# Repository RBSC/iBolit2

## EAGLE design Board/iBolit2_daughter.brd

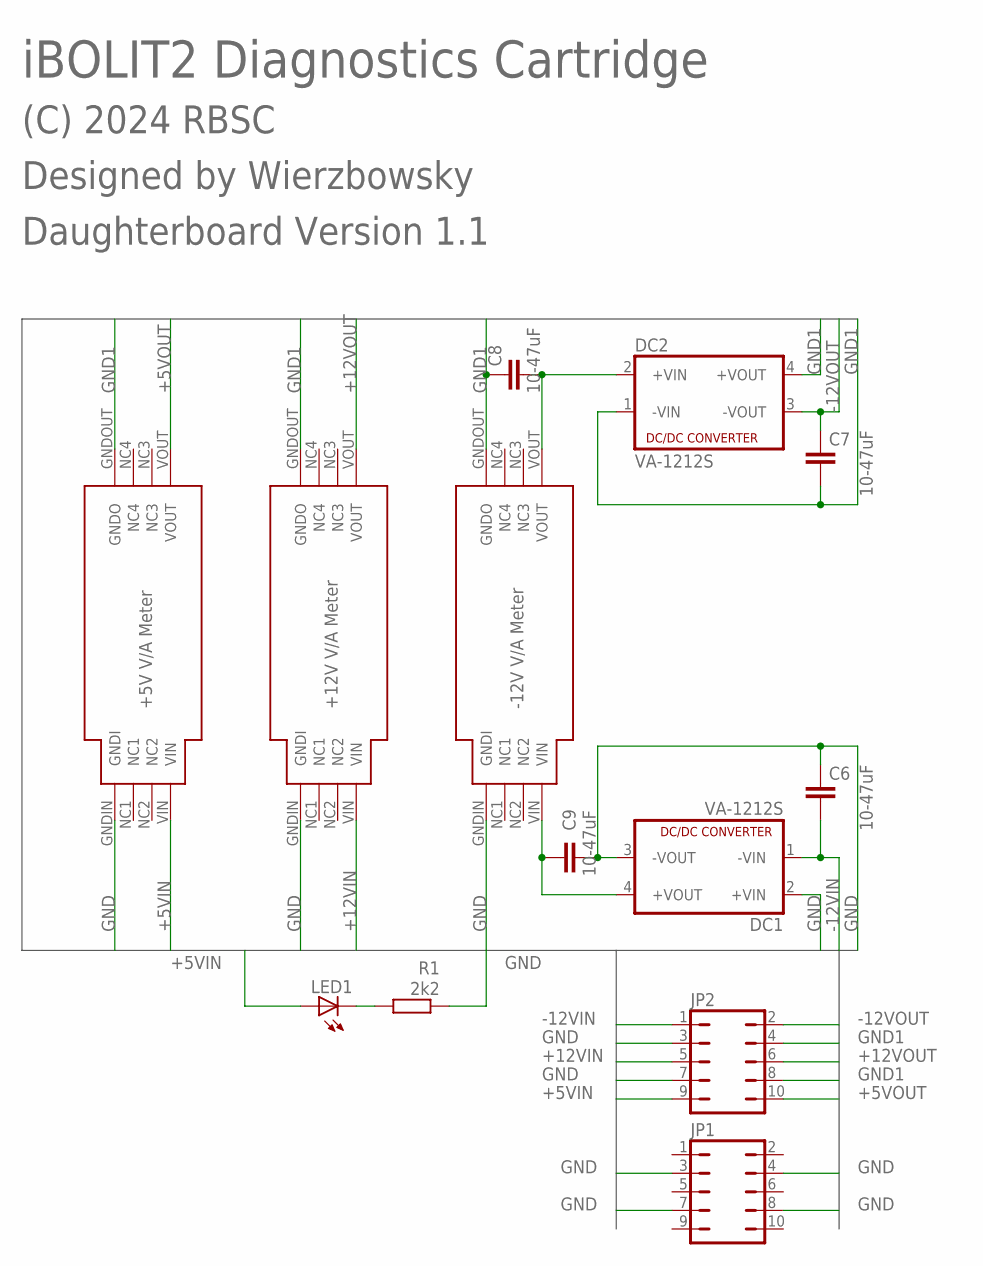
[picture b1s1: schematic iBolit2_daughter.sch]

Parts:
C6, C7, C8, C9: 10-47uF; C1210
DC1, DC2: VA-1212S; 4SIL
JP1, JP2: JP5Q_CUSTOM
LED1: LEDSQR2X5; LED2X5
R1: 2k2; R0805
X1, X2, X3: VA-METER2; VA_METER2

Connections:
+5VIN: JP2.9, LED1.A, X1.VIN
+5VOUT: JP2.10, X1.VOUT
+12VCONVI: C9.1, DC1.4 (+VOUT), X3.VIN
+12VCONVO: C8.2, DC2.2 (+VIN), X3.VOUT
+12VIN: JP2.5, X2.VIN
+12VOUT: JP2.6, X2.VOUT
-12VIN: C6.2, DC1.1 (-VIN), JP2.1
-12VOUT: C7.1, DC2.3 (-VOUT), JP2.2
GND: C6.1, C9.2, DC1.2 (+VIN), DC1.3 (-VOUT), JP1.3, JP1.4, JP1.7, JP1.8, JP2.3, JP2.7, R1.1, X1.GNDIN (GNDI), X2.GNDIN (GNDI), X3.GNDIN (GNDI)
GND1: C7.2, C8.1, DC2.1 (-VIN), DC2.4 (+VOUT), JP2.4, JP2.8, X1.GNDOUT (GNDO), X2.GNDOUT (GNDO), X3.GNDOUT (GNDO)
unnamed: LED1.K (C), R1.2

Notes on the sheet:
+5V V/A Meter
+12V V/A Meter
-12V V/A Meter
iBOLIT2 Diagnostics Cartridge
(C) 2024 RBSC
Designed by Wierzbowsky
Daughterboard Version 1.1

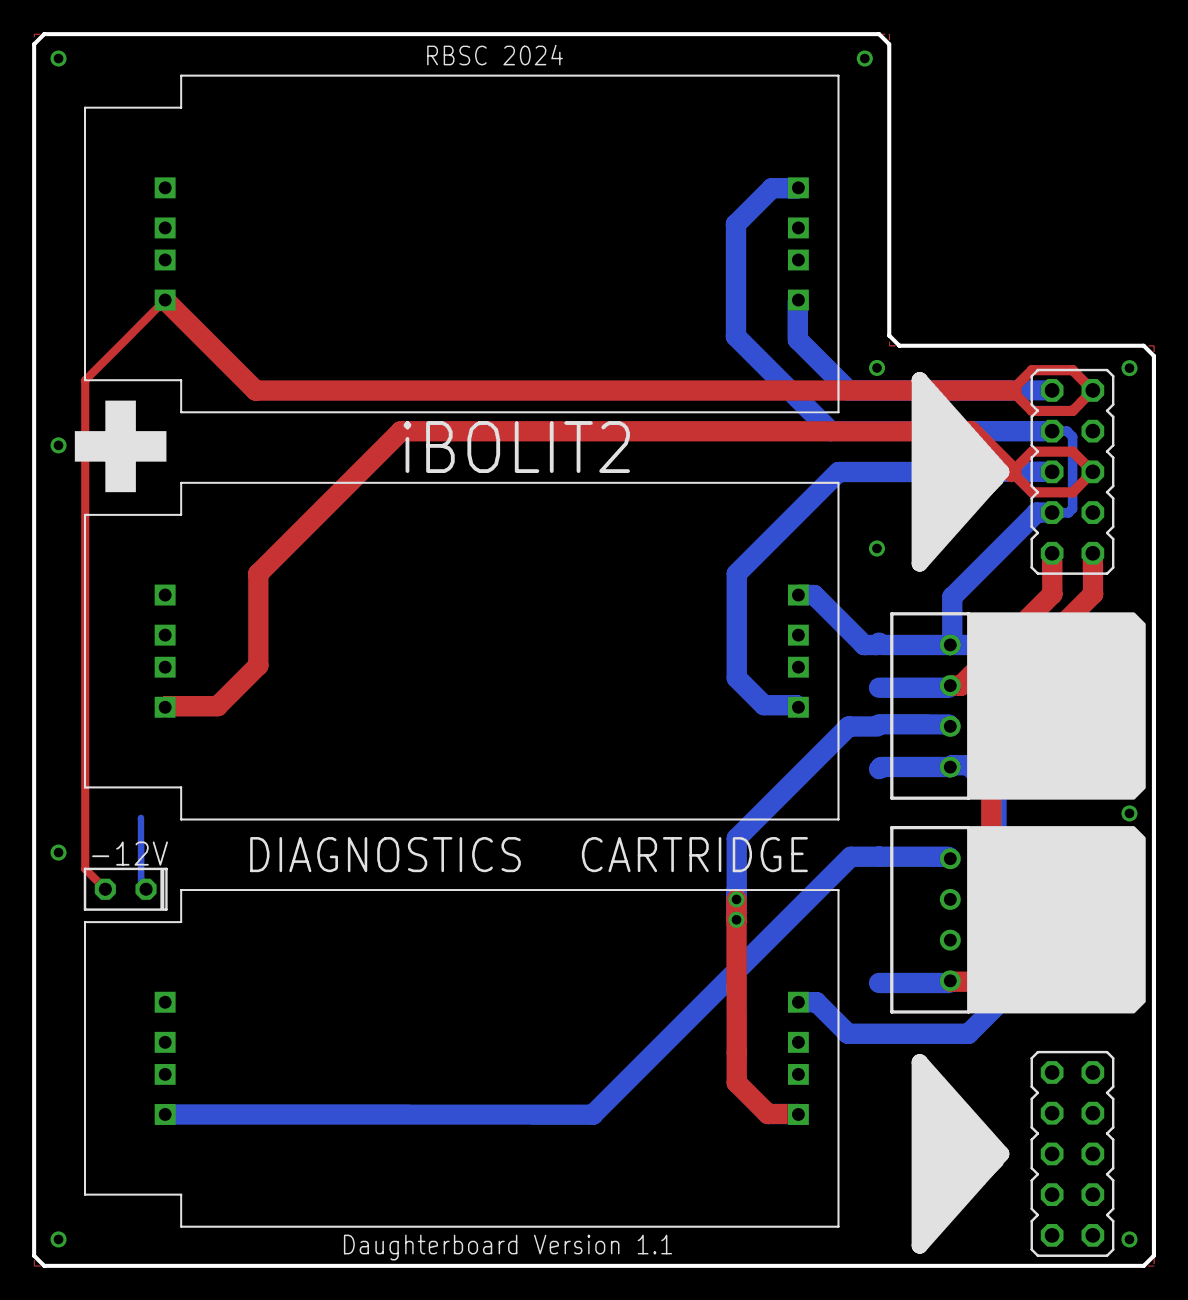
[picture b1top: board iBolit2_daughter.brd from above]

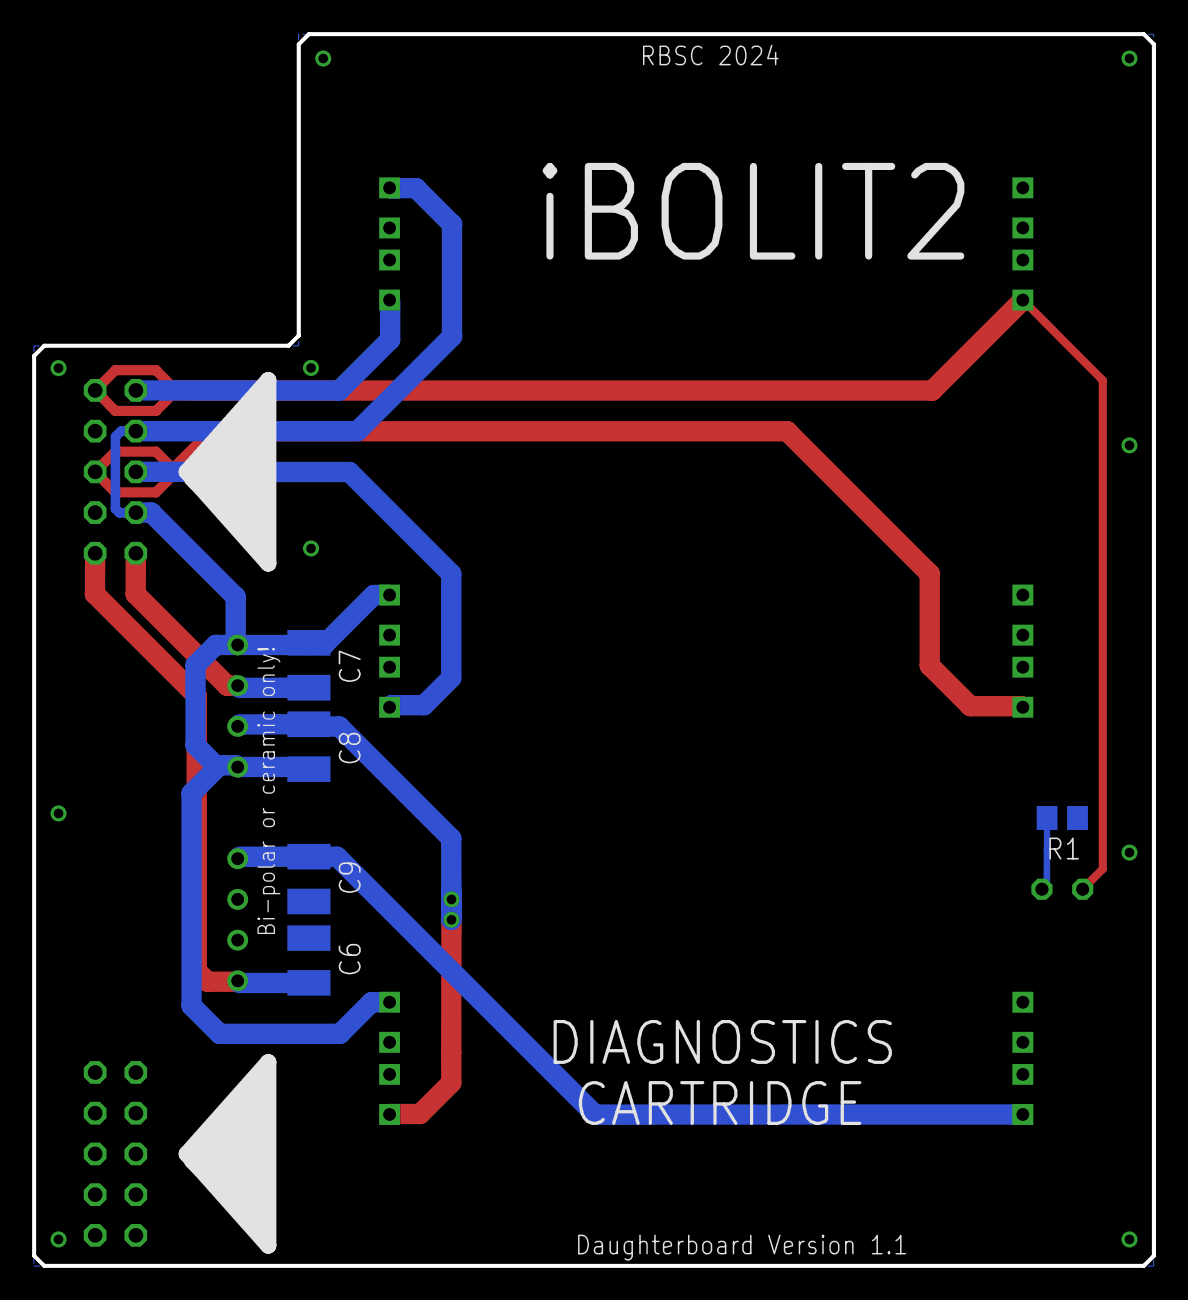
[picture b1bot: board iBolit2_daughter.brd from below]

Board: 2 copper layers, 69.8 x 76.8 mm, 13 parts (5 on the bottom side), 11 nets.

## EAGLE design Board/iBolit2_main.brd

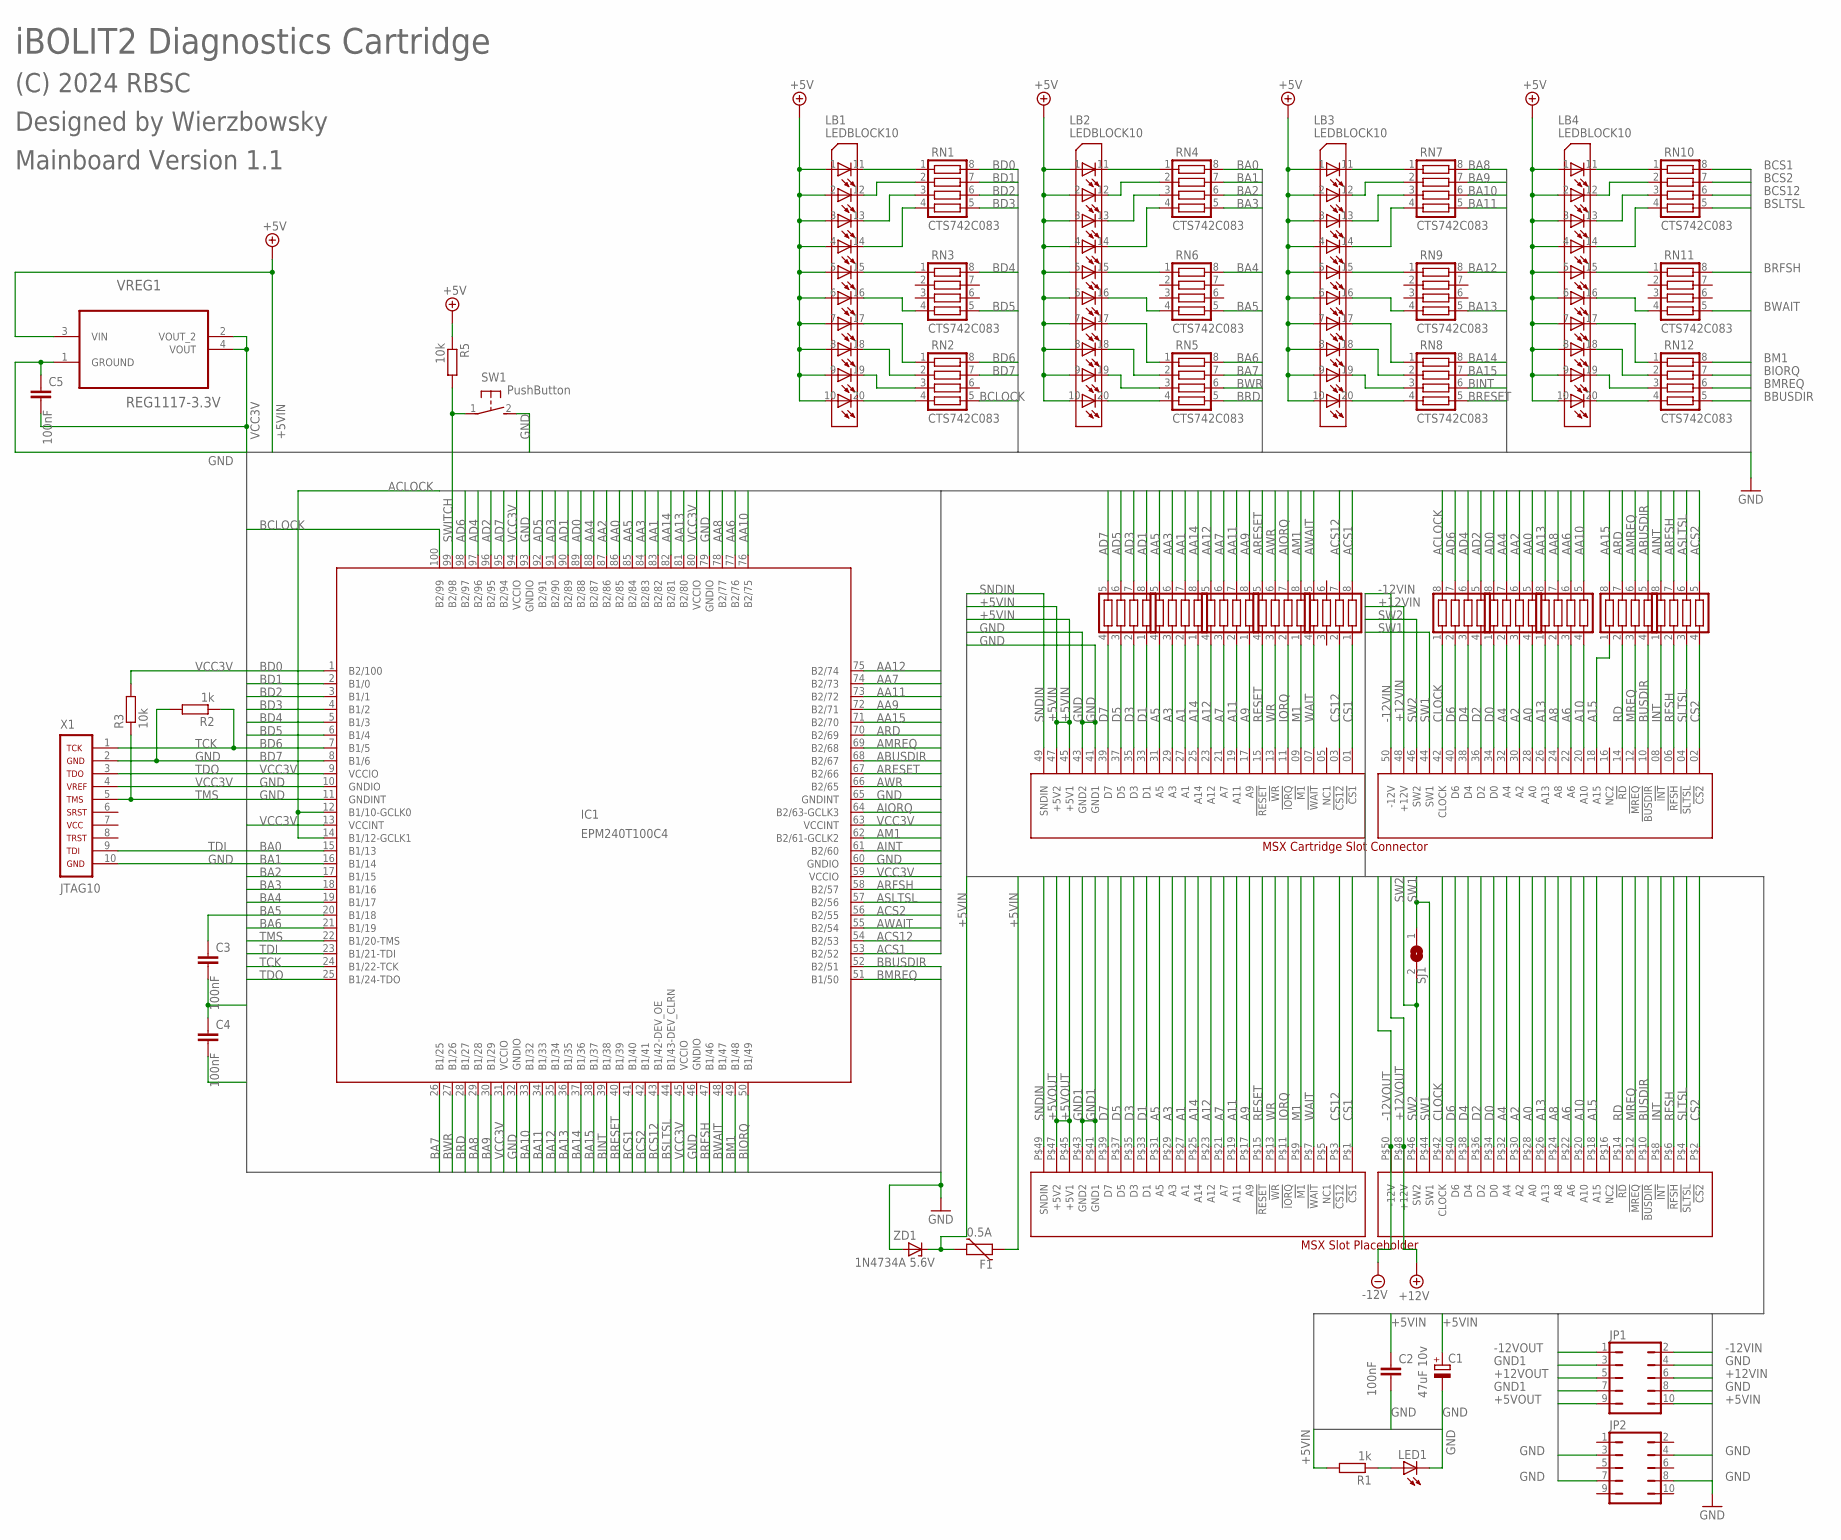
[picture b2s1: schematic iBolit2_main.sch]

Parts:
C1: 47uF 10v; SMC_B
C2, C3, C4, C5: 100nF; C0805
CN1: SLOTCONN; MSX_SLOT_CON
CN2: SLOTPLACEHOLDER; MSX_SLOT_PLP
F1: VARISTORCN1206; CT/CN1206
IC1: EPM240T100C4; TQFP100
JP1, JP2: JP5Q_CUSTOM
LB1, LB2, LB3, LB4: LEDBLOCK10; LB10
LED1: LED5MM
R1, R2: 1k; R0805
R3, R5: 10k; R0805
RN1, RN2, RN3, RN4, RN5, RN6, RN7, RN8, RN9, RN10, RN11, RN12, RN13, RN14, RN15, RN16, RN17, RN28, RN29, RN30, RN31, RN32: CTS742C083
SJ1: SJ
SW1: PushButton; B3F-31XX
VREG1: REG1117-3.3V; SOT230P700X180-4N
X1: JTAG10
ZD1: 1N4734A 5.6V; ZDIO-7.5

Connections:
+5VIN: C1.+, C2.1, CN1.45 (+5V1), CN1.47 (+5V2), F1.1, F1.2, JP1.10, LB1.1 (L1I), LB1.2 (L1I1), LB1.3 (L1I2), LB1.4 (L1I3), LB1.5 (L1I4), LB1.6 (L1I5), LB1.7 (L1I6), LB1.8 (L1I7), LB1.9 (L1I8), LB1.10 (L1I9), LB2.1 (L1I), LB2.2 (L1I1), LB2.3 (L1I2), LB2.4 (L1I3), LB2.5 (L1I4), LB2.6 (L1I5), LB2.7 (L1I6), LB2.8 (L1I7), LB2.9 (L1I8), LB2.10 (L1I9), LB3.1 (L1I), LB3.2 (L1I1), LB3.3 (L1I2), LB3.4 (L1I3), LB3.5 (L1I4), LB3.6 (L1I5), LB3.7 (L1I6), LB3.8 (L1I7), LB3.9 (L1I8), LB3.10 (L1I9), LB4.1 (L1I), LB4.2 (L1I1), LB4.3 (L1I2), LB4.4 (L1I3), LB4.5 (L1I4), LB4.6 (L1I5), LB4.7 (L1I6), LB4.8 (L1I7), LB4.9 (L1I8), LB4.10 (L1I9), R1.2, R5.1, VREG1.3 (VIN), ZD1.C
+5VOUT: CN2.P$45 (+5V1), CN2.P$47 (+5V2), JP1.9
+12VIN: CN1.48 (+12V), JP1.6
+12VOUT: CN2.P$48 (+12V), JP1.5
-12VIN: CN1.50 (-12V), JP1.2
-12VOUT: CN2.P$50 (-12V), JP1.1
A0: CN1.28 (A0), CN2.P$28 (A0), RN29.4
A1: CN1.27 (A1), CN2.P$27 (A1), RN16.2
A2: CN1.30 (A2), CN2.P$30 (A2), RN29.3
A3: CN1.29 (A3), CN2.P$29 (A3), RN16.3
A4: CN1.32 (A4), CN2.P$32 (A4), RN29.2
A5: CN1.31 (A5), CN2.P$31 (A5), RN16.4
A6: CN1.22 (A6), CN2.P$22 (A6), RN30.3
A7: CN1.21 (A7), CN2.P$21 (A7), RN15.3
A8: CN1.24 (A8), CN2.P$24 (A8), RN30.2
A9: CN1.17 (A9), CN2.P$17 (A9), RN15.1
A10: CN1.20 (A10), CN2.P$20 (A10), RN30.4
A11: CN1.19 (A11), CN2.P$19 (A11), RN15.2
A12: CN1.23 (A12), CN2.P$23 (A12), RN15.4
A13: CN1.26 (A13), CN2.P$26 (A13), RN30.1
A14: CN1.25 (A14), CN2.P$25 (A14), RN16.1
A15: CN1.18 (A15), CN2.P$18 (A15), RN32.1
AA0: IC1.86 (B2/85), RN29.5
AA1: IC1.83 (B2/82), RN16.7
AA2: IC1.87 (B2/86), RN29.6
AA3: IC1.84 (B2/83), RN16.6
AA4: IC1.88 (B2/87), RN29.7
AA5: IC1.85 (B2/84), RN16.5
AA6: IC1.77 (B2/76), RN30.6
AA7: IC1.74 (B2/73), RN15.6
AA8: IC1.78 (B2/77), RN30.7
AA9: IC1.72 (B2/71), RN15.8
AA10: IC1.76 (B2/75), RN30.5
AA11: IC1.73 (B2/72), RN15.7
AA12: IC1.75 (B2/74), RN15.5
AA13: IC1.81 (B2/80), RN30.8
AA14: IC1.82 (B2/81), RN16.8
AA15: IC1.71 (B2/70), RN32.8
ABUSDIR: IC1.68 (B2/67), RN32.5
ACLOCK: IC1.12 (B1/10-GCLK0), IC1.14 (B1/12-GCLK1), RN28.8
ACS1: IC1.53 (B2/52), RN13.8
ACS2: IC1.56 (B2/55), RN31.5
ACS12: IC1.54 (B2/53), RN13.7
AD0: IC1.89 (B2/88), RN29.8
AD1: IC1.90 (B2/89), RN17.8
AD2: IC1.96 (B2/95), RN28.5
AD3: IC1.91 (B2/90), RN17.7
AD4: IC1.97 (B2/96), RN28.6
AD5: IC1.92 (B2/91), RN17.6
AD6: IC1.98 (B2/97), RN28.7
AD7: IC1.95 (B2/94), RN17.5
AINT: IC1.61 (B2/60), RN31.8
AIORQ: IC1.64 (B2/63-GCLK3), RN14.7
AM1: IC1.62 (B2/61-GCLK2), RN14.8
AMREQ: IC1.69 (B2/68), RN32.6
ARD: IC1.70 (B2/69), RN32.7
ARESET: IC1.67 (B2/66), RN14.5
ARFSH: IC1.58 (B2/57), RN31.7
ASLTSL: IC1.57 (B2/56), RN31.6
AWAIT: IC1.55 (B2/54), RN13.5
AWR: IC1.66 (B2/65), RN14.6
BA0: IC1.15 (B1/13), RN4.8
BA1: IC1.16 (B1/14), RN4.7
BA2: IC1.17 (B1/15), RN4.6
BA3: IC1.18 (B1/16), RN4.5
BA4: IC1.19 (B1/17), RN6.8
BA5: IC1.20 (B1/18), RN6.5
BA6: IC1.21 (B1/19), RN5.8
BA7: IC1.26 (B1/25), RN5.7
BA8: IC1.29 (B1/28), RN7.8
BA9: IC1.30 (B1/29), RN7.7
BA10: IC1.33 (B1/32), RN7.6
BA11: IC1.34 (B1/33), RN7.5
BA12: IC1.35 (B1/34), RN9.8
BA13: IC1.36 (B1/35), RN9.5
BA14: IC1.37 (B1/36), RN8.8
BA15: IC1.38 (B1/37), RN8.7
BBUSDIR: IC1.52 (B2/51), RN12.5
BCLOCK: IC1.100 (B2/99), RN2.5
BCS1: IC1.41 (B1/40), RN10.8
BCS2: IC1.42 (B1/41), RN10.7
BCS12: IC1.43 (B1/42-DEV_OE), RN10.6
BD0: IC1.1 (B2/100), RN1.8
BD1: IC1.2 (B1/0), RN1.7
BD2: IC1.3 (B1/1), RN1.6
BD3: IC1.4 (B1/2), RN1.5
BD4: IC1.5 (B1/3), RN3.8
BD5: IC1.6 (B1/4), RN3.5
BD6: IC1.7 (B1/5), RN2.8
BD7: IC1.8 (B1/6), RN2.7
BINT: IC1.39 (B1/38), RN8.6
BIORQ: IC1.50 (B1/49), RN12.7
BM1: IC1.49 (B1/48), RN12.8
BMREQ: IC1.51 (B1/50), RN12.6
BRD: IC1.28 (B1/27), RN5.5
BRESET: IC1.40 (B1/39), RN8.5
BRFSH: IC1.47 (B1/46), RN11.8
BSLTSL: IC1.44 (B1/43-DEV_CLRN), RN10.5
BUSDIR: CN1.10 (!BUSDIR), CN2.P$10 (!BUSDIR), RN32.4
BWAIT: IC1.48 (B1/47), RN11.5
BWR: IC1.27 (B1/26), RN5.6
CLOCK: CN1.42 (CLOCK), CN2.P$42 (CLOCK), RN28.1
CS1: CN1.01 (!CS1), CN2.P$1 (!CS1), RN13.1
CS2: CN1.02 (!CS2), CN2.P$2 (!CS2), RN31.4
CS12: CN1.03 (!CS12), CN2.P$3 (!CS12), RN13.2
D0: CN1.34 (D0), CN2.P$34 (D0), RN29.1
D1: CN1.33 (D1), CN2.P$33 (D1), RN17.1
D2: CN1.36 (D2), CN2.P$36 (D2), RN28.4
D3: CN1.35 (D3), CN2.P$35 (D3), RN17.2
D4: CN1.38 (D4), CN2.P$38 (D4), RN28.3
D5: CN1.37 (D5), CN2.P$37 (D5), RN17.3
D6: CN1.40 (D6), CN2.P$40 (D6), RN28.2
D7: CN1.39 (D7), CN2.P$39 (D7), RN17.4
GND: C1.-, C2.2, C3.2, C4.1, C5.1, CN1.41 (GND1), CN1.43 (GND2), IC1.10 (GNDIO), IC1.11 (GNDINT), IC1.32 (GNDIO), IC1.46 (GNDIO), IC1.60 (GNDIO), IC1.65 (GNDINT), IC1.79 (GNDIO), IC1.93 (GNDIO), JP1.4, JP1.8, JP2.3, JP2.4, JP2.7, JP2.8, LED1.K (C), R2.2, SW1.2 (S), VREG1.1 (GROUND), X1.2, X1.10, ZD1.A
GND1: CN2.P$41 (GND1), CN2.P$43 (GND2), JP1.3, JP1.7
INT: CN1.08 (!INT), CN2.P$8 (!INT), RN31.1
IORQ: CN1.11 (!IORQ), CN2.P$11 (!IORQ), RN14.2
M1: CN1.09 (!M1), CN2.P$9 (!M1), RN14.1
MREQ: CN1.12 (!MREQ), CN2.P$12 (!MREQ), RN32.3
unnamed: LED1.A, R1.1
unnamed: LB4.11 (L1O), RN10.1
unnamed: LB4.12 (L1O1), RN10.2
unnamed: LB4.13 (L1O2), RN10.3
unnamed: LB4.14 (L1O3), RN10.4
unnamed: LB4.15 (L1O4), RN11.1
unnamed: LB4.16 (L1O5), RN11.4
unnamed: LB4.17 (L1O6), RN12.1
unnamed: LB4.18 (L1O7), RN12.2
unnamed: LB4.19 (L1O8), RN12.3
unnamed: LB4.20 (L1O9), RN12.4
unnamed: LB1.11 (L1O), RN1.1
unnamed: LB1.12 (L1O1), RN1.2
unnamed: LB1.13 (L1O2), RN1.3
unnamed: LB1.14 (L1O3), RN1.4
unnamed: LB1.15 (L1O4), RN3.1
unnamed: LB1.16 (L1O5), RN3.4
unnamed: LB1.17 (L1O6), RN2.1
unnamed: LB1.18 (L1O7), RN2.2
unnamed: LB1.19 (L1O8), RN2.3
unnamed: LB1.20 (L1O9), RN2.4
unnamed: LB2.11 (L1O), RN4.1
unnamed: LB2.12 (L1O1), RN4.2
unnamed: LB2.13 (L1O2), RN4.3
unnamed: LB2.14 (L1O3), RN4.4
unnamed: LB2.15 (L1O4), RN6.1
unnamed: LB2.16 (L1O5), RN6.4
unnamed: LB2.17 (L1O6), RN5.1
unnamed: LB2.18 (L1O7), RN5.2
unnamed: LB2.19 (L1O8), RN5.3
unnamed: LB2.20 (L1O9), RN5.4
unnamed: LB3.11 (L1O), RN7.1
unnamed: LB3.12 (L1O1), RN7.2
unnamed: LB3.13 (L1O2), RN7.3
unnamed: LB3.14 (L1O3), RN7.4
unnamed: LB3.15 (L1O4), RN9.1
unnamed: LB3.16 (L1O5), RN9.4
unnamed: LB3.17 (L1O6), RN8.1
unnamed: LB3.18 (L1O7), RN8.2
unnamed: LB3.19 (L1O8), RN8.3
unnamed: LB3.20 (L1O9), RN8.4
RD: CN1.14 (!RD), CN2.P$14 (!RD), RN32.2
RESET: CN1.15 (!RESET), CN2.P$15 (!RESET), RN14.4
RFSH: CN1.06 (!RFSH), CN2.P$6 (!RFSH), RN31.2
SLTSL: CN1.04 (!SLTSL), CN2.P$4 (!SLTSL), RN31.3
SNDIN: CN1.49 (SNDIN), CN2.P$49 (SNDIN)
SW1: CN1.44 (SW1), CN2.P$44 (SW1), SJ1.1
SW2: CN1.46 (SW2), CN2.P$46 (SW2), SJ1.2
SWITCH: IC1.99 (B2/98), R5.2, SW1.1
TCK: IC1.24 (B1/22-TCK), R2.1, X1.1
TDI: IC1.23 (B1/21-TDI), X1.9
TDO: IC1.25 (B1/24-TDO), X1.3
TMS: IC1.22 (B1/20-TMS), R3.1, X1.5
VCC3V: C3.1, C4.2, C5.2, IC1.9 (VCCIO), IC1.13 (VCCINT), IC1.31 (VCCIO), IC1.45 (VCCIO), IC1.59 (VCCIO), IC1.63 (VCCINT), IC1.80 (VCCIO), IC1.94 (VCCIO), R3.2, VREG1.2 (VOUT_2), VREG1.4 (VOUT), X1.4
WAIT: CN1.07 (!WAIT), CN2.P$7 (!WAIT), RN13.4
WR: CN1.13 (!WR), CN2.P$13 (!WR), RN14.3

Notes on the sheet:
iBOLIT2 Diagnostics Cartridge
(C) 2024 RBSC
Designed by Wierzbowsky
Mainboard Version 1.1
0.5A

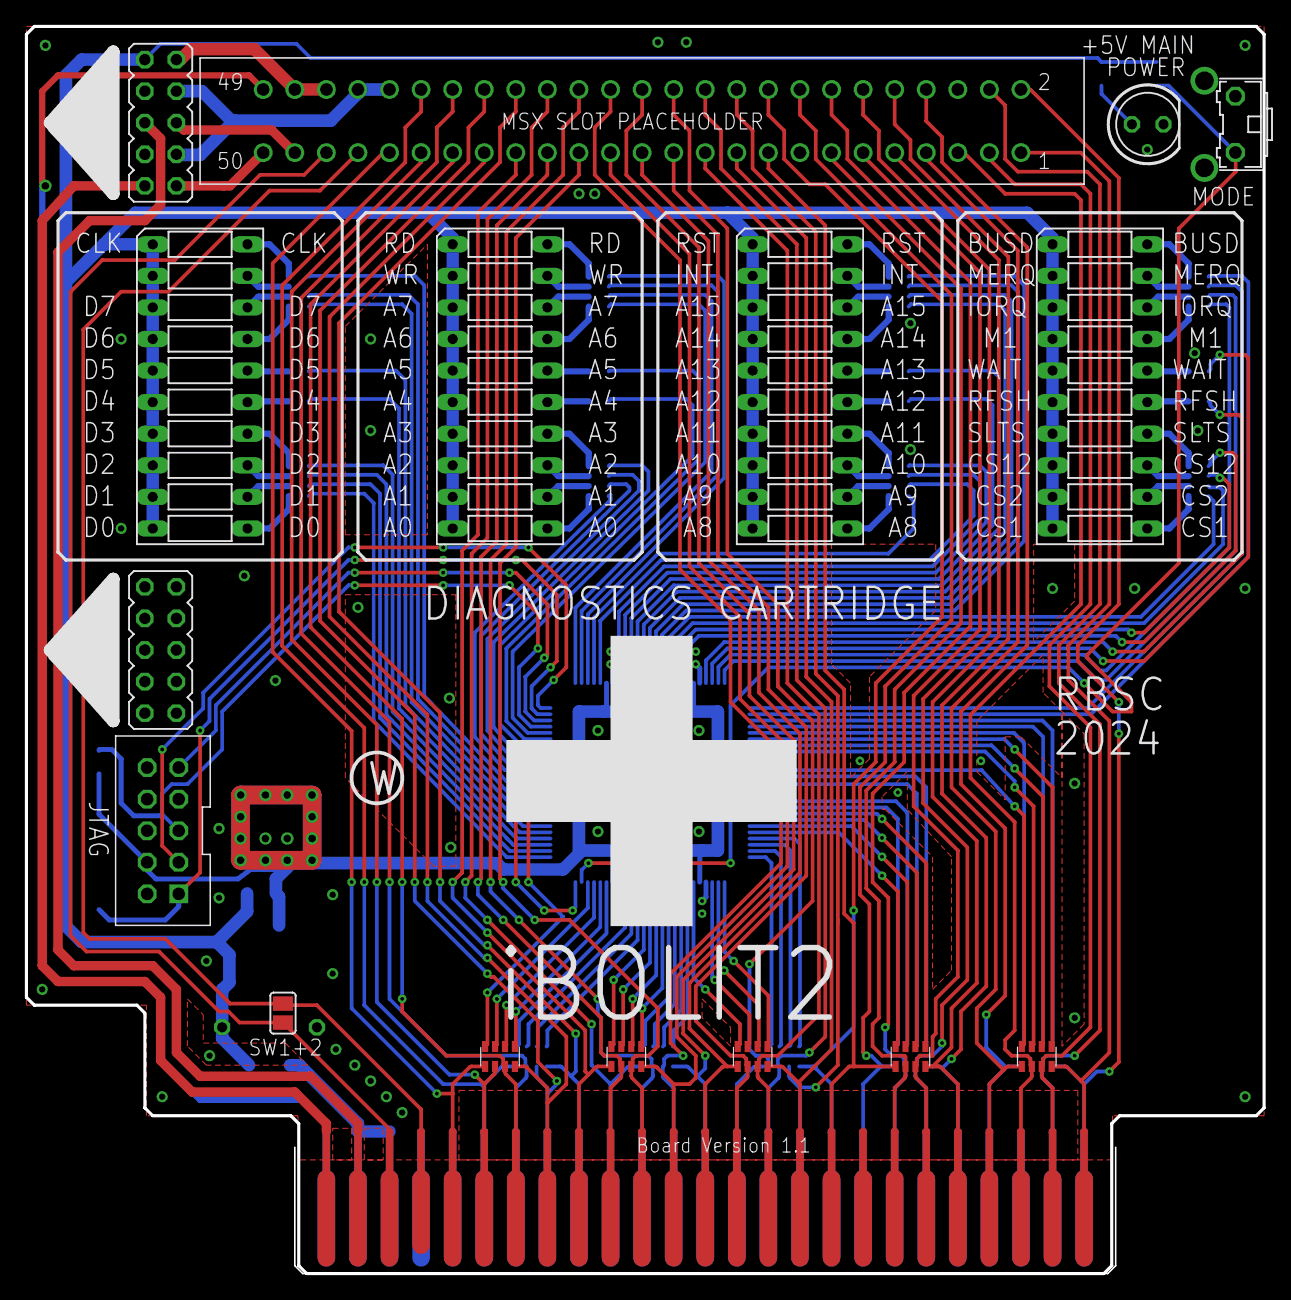
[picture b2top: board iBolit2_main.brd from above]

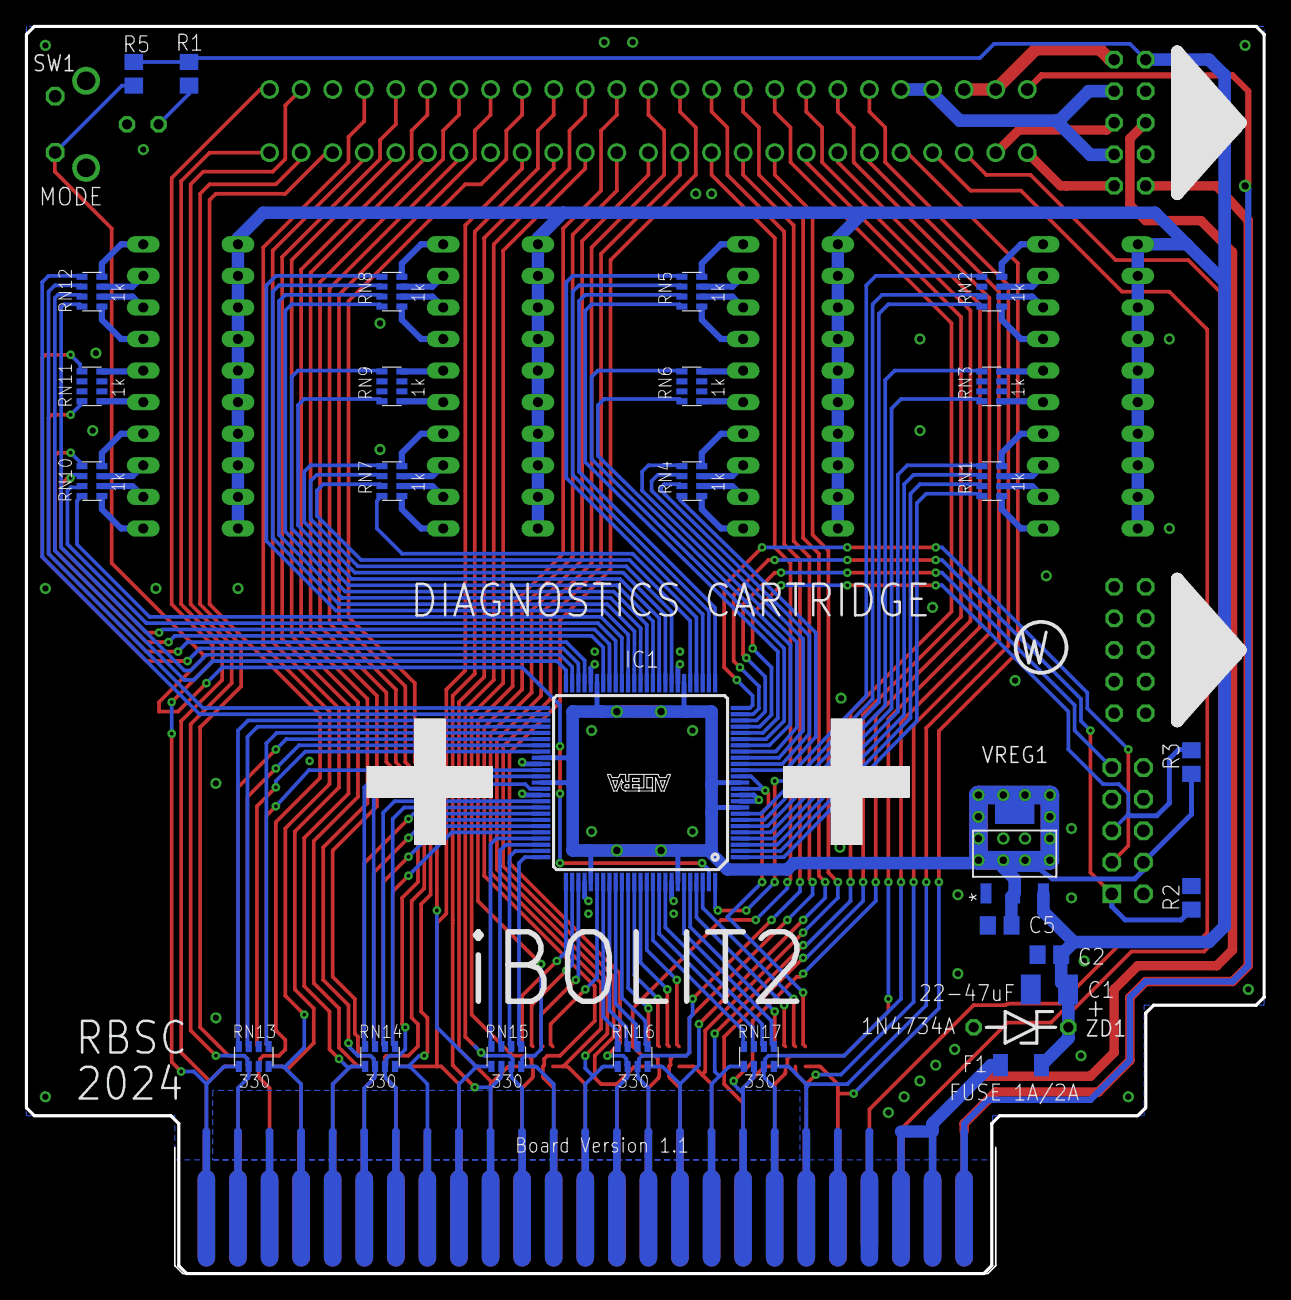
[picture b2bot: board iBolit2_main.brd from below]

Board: 2 copper layers, 99.6 x 100.3 mm, 47 parts (28 on the bottom side), 175 nets.

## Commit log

2025-06-19 Initial release 19.06.2025
    The initial release of iBolit2 files.

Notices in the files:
parts and their libraries:
JTAG: Copyright (C) 2010 Michel Catudal mcatudal@comcast.net
